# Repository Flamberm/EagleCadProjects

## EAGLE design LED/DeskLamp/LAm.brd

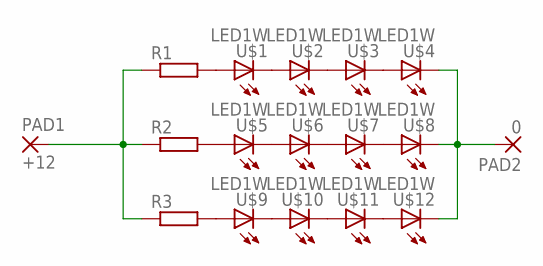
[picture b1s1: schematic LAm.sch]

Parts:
PAD1: +12; SMD2,54-5,08
PAD2: 0; SMD2,54-5,08
R1, R2, R3: R-EU_R0805; R0805
U$1, U$2, U$3, U$4, U$5, U$6, U$7, U$8, U$9, U$10, U$11, U$12: LED1W; LED-1W

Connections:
unnamed: R1.2, U$1.A
unnamed: U$1.K (C), U$2.A
unnamed: U$2.K (C), U$3.A
unnamed: U$3.K (C), U$4.A
unnamed: R2.2, U$5.A
unnamed: U$5.K (C), U$6.A
unnamed: U$6.K (C), U$7.A
unnamed: U$7.K (C), U$8.A
unnamed: R3.2, U$9.A
unnamed: U$9.K (C), U$10.A
unnamed: U$10.K (C), U$11.A
unnamed: U$11.K (C), U$12.A
unnamed: PAD1.1, R1.1, R2.1, R3.1
unnamed: PAD2.1, U$4.K (C), U$8.K (C), U$12.K (C)

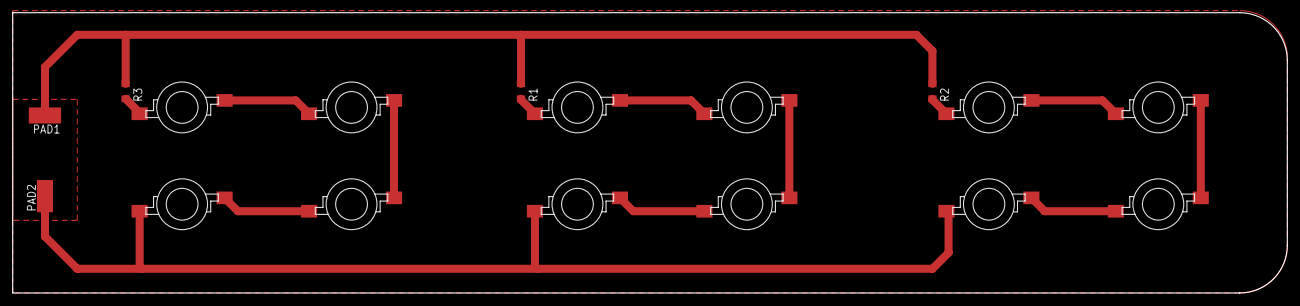
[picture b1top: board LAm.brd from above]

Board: 2 copper layers, 200.6 x 44.1 mm, 17 parts (0 on the bottom side), 14 nets.

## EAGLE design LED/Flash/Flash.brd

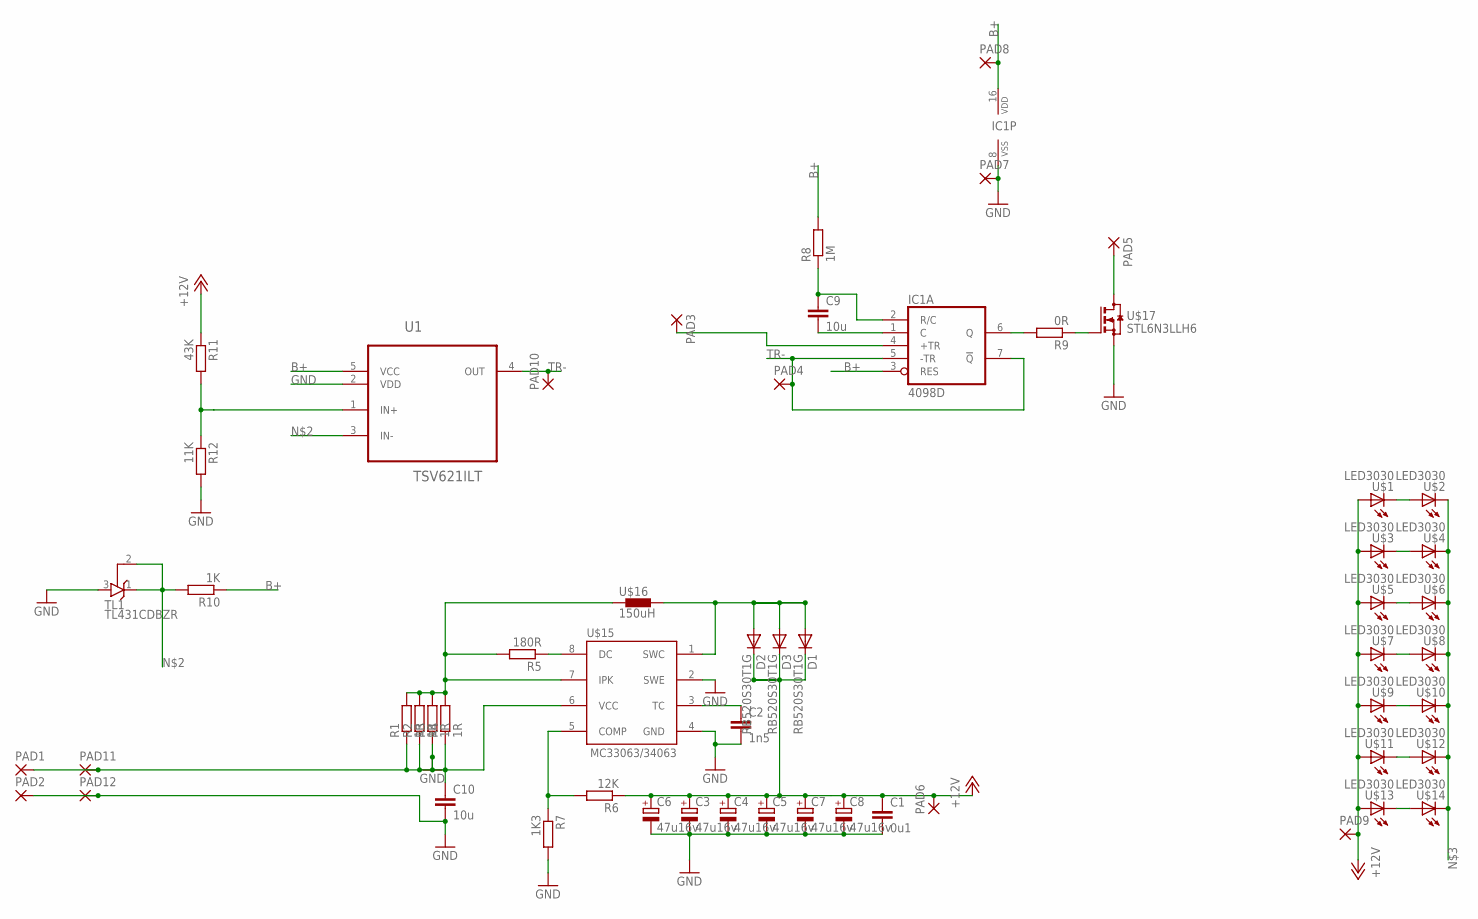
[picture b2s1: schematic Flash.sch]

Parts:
C1: 0u1; C0805
C2: 1n5; C0805
C3, C4, C5, C6, C7, C8: 47u16v; 153CLV-0605
C9: 10u; C0805
C10: 10u; C1206
D1, D2, D3: RB520S30T1G; SOD523
IC1: 4098D; SO16
PAD1, PAD2, PAD3, PAD4, PAD5, PAD6, PAD7, PAD8, PAD9, PAD10, PAD11, PAD12: SMD2; SMD1,27-2,54
R1, R2, R3, R4: 1R; R0805
R5: 180R; R0805
R6: 12K; R0805
R7: 1K3; R0805
R8: 1M; R0805
R9: 0R; R0805
R10: 1K; R0805
R11: 43K; R0805
R12: 11K; R0805
TL1: TL431CDBZR; SOT23
U1: TSV621ILT; SOT95P280X145-5N
U$1, U$2, U$3, U$4, U$5, U$6, U$7, U$8, U$9, U$10, U$11, U$12, U$13, U$14: LED3030
U$15: MC33063/MC34063D; SO08
U$16: 150uH; L6045
U$17: STL6N3LLH6; POWERFLAT-2X2

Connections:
+12V: C1.1, C3.+, C4.+, C5.+, C6.+, C7.+, C8.+, D1.C, D2.C, D3.C, PAD6.1, PAD9.1, R6.1, R11.1, U$1.P$1 (A), U$3.P$1 (A), U$5.P$1 (A), U$7.P$1 (A), U$9.P$1 (A), U$11.P$1 (A), U$13.P$1 (A)
B+: C10.1, IC1.3 (RES), IC1.16 (VDD), PAD1.1, PAD8.1, PAD11.1, R1.1, R2.1, R3.1, R4.1, R8.2, R10.1, U1.5 (VCC), U$15.6 (VCC)
GND: C1.2, C2.2, C3.-, C4.-, C5.-, C6.-, C7.-, C8.-, C10.2, IC1.8 (VSS), PAD2.1, PAD7.1, PAD12.1, R7.2, R12.2, TL1.3 (A), U1.2 (VDD), U$15.2 (SWE), U$15.4 (GND), U$17.S, U$17.S4 (S)
unnamed: U$1.P$2 (C), U$2.P$1 (A)
unnamed: R10.2, TL1.1 (C), TL1.2 (R), U1.3 (IN-)
unnamed: PAD5.1, U$2.P$2 (C), U$4.P$2 (C), U$6.P$2 (C), U$8.P$2 (C), U$10.P$2 (C), U$12.P$2 (C), U$14.P$2 (C), U$17.D, U$17.D1 (D), U$17.D2 (D), U$17.D5 (D), U$17.D6 (D)
unnamed: U$3.P$2 (C), U$4.P$1 (A)
unnamed: R11.2, R12.1, U1.1 (IN+)
unnamed: IC1.4 (+TR), PAD3.1
unnamed: U$5.P$2 (C), U$6.P$1 (A)
unnamed: R1.2, R2.2, R3.2, R4.2, R5.2, U$15.7 (IPK), U$16.P$1 (1)
unnamed: R5.1, U$15.8 (DC)
unnamed: U$7.P$2 (C), U$8.P$1 (A)
unnamed: R6.2, R7.1, U$15.5 (COMP)
unnamed: D1.A, D2.A, D3.A, U$15.1 (SWC), U$16.P$2 (2)
unnamed: U$9.P$2 (C), U$10.P$1 (A)
unnamed: C2.1, U$15.3 (TC)
unnamed: U$11.P$2 (C), U$12.P$1 (A)
unnamed: C9.2, IC1.1 (C)
unnamed: C9.1, IC1.2 (R/C), R8.1
unnamed: U$13.P$2 (C), U$14.P$1 (A)
unnamed: IC1.6 (Q), R9.2
unnamed: R9.1, U$17.G3 (G)
TR-: IC1.5 (-TR), IC1.7 (!Q), PAD4.1, PAD10.1, U1.4 (OUT)

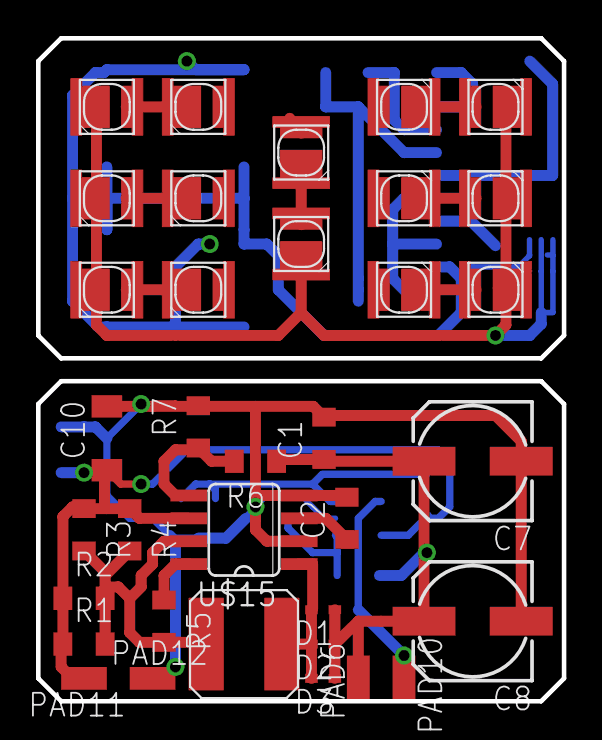
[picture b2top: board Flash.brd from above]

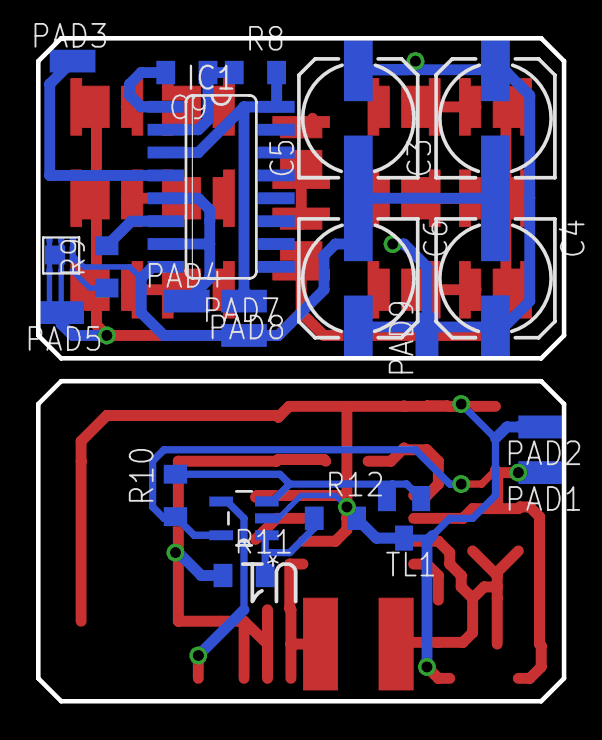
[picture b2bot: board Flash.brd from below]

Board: 2 copper layers, 29.2 x 36.8 mm, 57 parts (22 on the bottom side), 24 nets.

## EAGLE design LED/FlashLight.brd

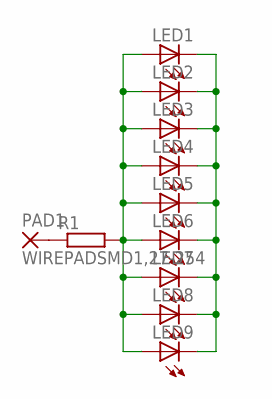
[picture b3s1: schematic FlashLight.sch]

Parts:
LED1, LED2, LED3, LED4, LED5, LED6, LED7, LED8, LED9: LED5MM
PAD1: WIREPADSMD1,27-254; SMD1,27-2,54
R1: R-EU_R1206; R1206

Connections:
unnamed: LED1.A, LED2.A, LED3.A, LED4.A, LED5.A, LED6.A, LED7.A, LED8.A, LED9.A, R1.2
unnamed: LED1.K (C), LED2.K (C), LED3.K (C), LED4.K (C), LED5.K (C), LED6.K (C), LED7.K (C), LED8.K (C), LED9.K (C)
unnamed: PAD1.1, R1.1

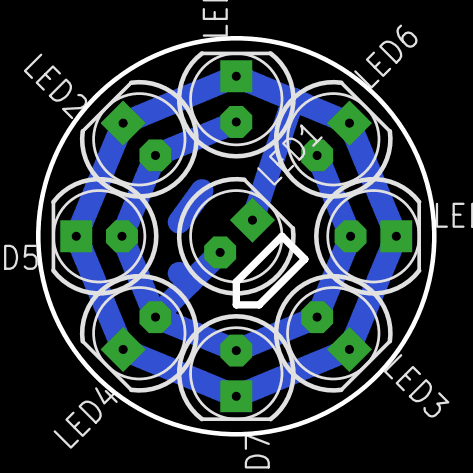
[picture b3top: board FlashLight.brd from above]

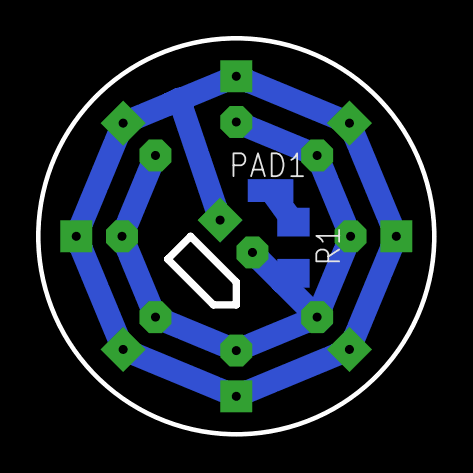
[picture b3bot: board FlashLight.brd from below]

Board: 2 copper layers, 22.0 x 22.0 mm, 11 parts (2 on the bottom side), 3 nets.

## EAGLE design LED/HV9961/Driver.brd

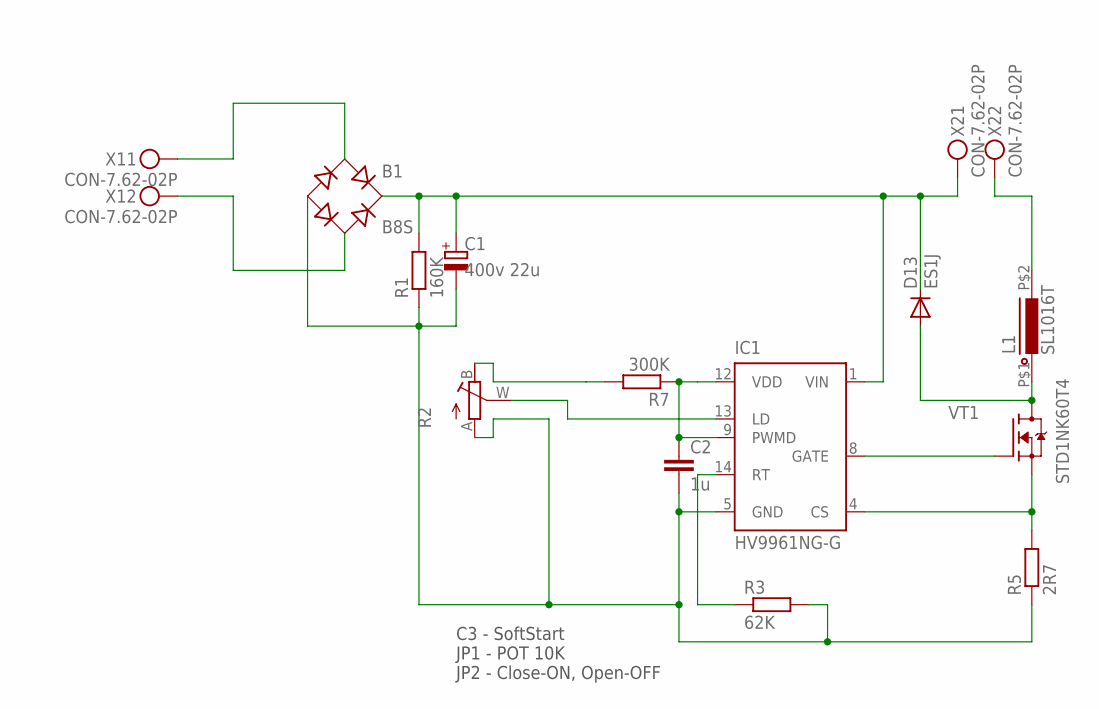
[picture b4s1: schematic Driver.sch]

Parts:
B1: B8S; DFS
C1: 400v 22u; E3,5-8
C2: 1u; C0805
D13: ES1J; DO214AC
IC1: HV9961NG-G; SOIC-16NG
L1: SL1016T; SL1016
R1: 160K; MF-0125
R2: R_POTTURN-X; RJ9W
R3: 62K; R0805
R5: 2R7; MF-025
R7: 300K; R0805
VT1: STD1NK60T4; DPAK
X1, X2: CON-7.62-02P; KF25C-7.62-02P-13

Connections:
unnamed: R2.B (E), R7.2
unnamed: C2.1, IC1.9 (PWMD), IC1.12 (VDD), R7.1
unnamed: B1.AC1, X1.P$1
unnamed: B1.AC2, X1.P$2
unnamed: B1.-, C1.-, C2.2, IC1.5 (GND), R1.1, R2.A, R3.2, R5.1
unnamed: IC1.13 (LD), R2.W (S)
unnamed: B1.+, C1.+, D13.C, IC1.1 (VIN), R1.2, X2.P$1
unnamed: IC1.4 (CS), R5.2, VT1.S
unnamed: IC1.14 (RT), R3.1
unnamed: IC1.8 (GATE), VT1.G
unnamed: L1.P$2 (2), X2.P$2
unnamed: D13.A, L1.P$1 (1), VT1.D

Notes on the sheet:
C3 - SoftStart JP1 - POT 10K JP2 - Close-ON, Open-OFF

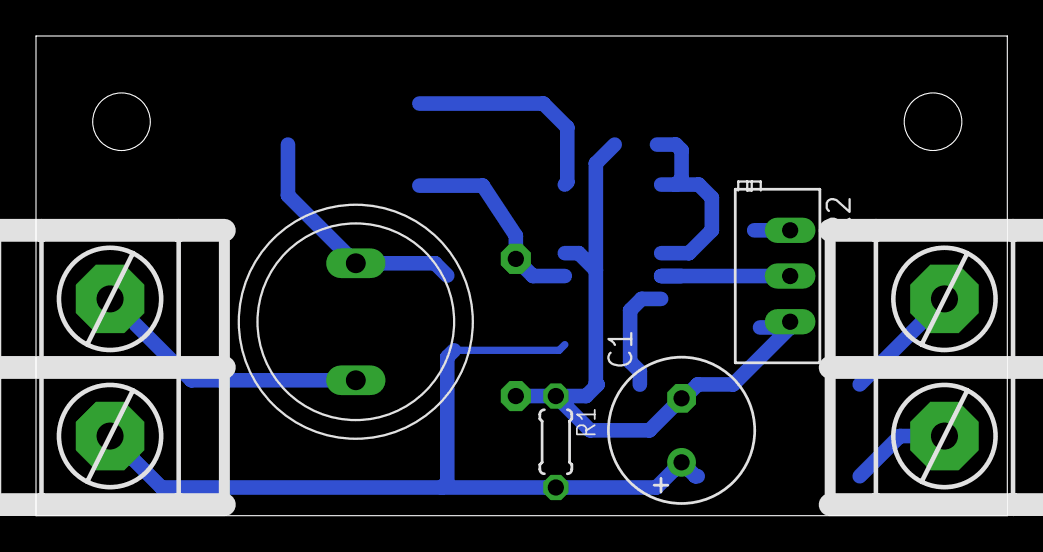
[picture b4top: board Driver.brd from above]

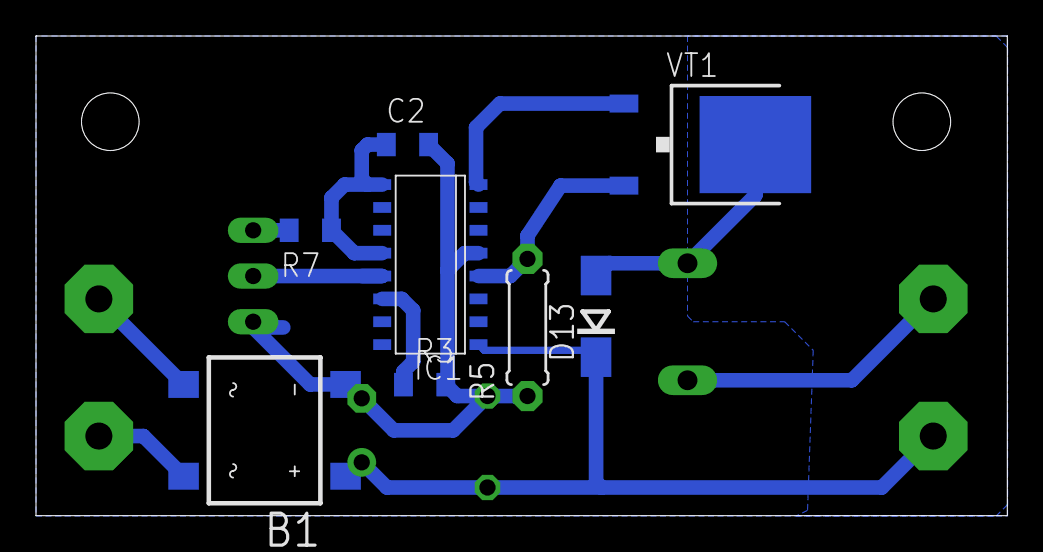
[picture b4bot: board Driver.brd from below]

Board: 2 copper layers, 54.0 x 26.7 mm, 14 parts (8 on the bottom side), 12 nets.

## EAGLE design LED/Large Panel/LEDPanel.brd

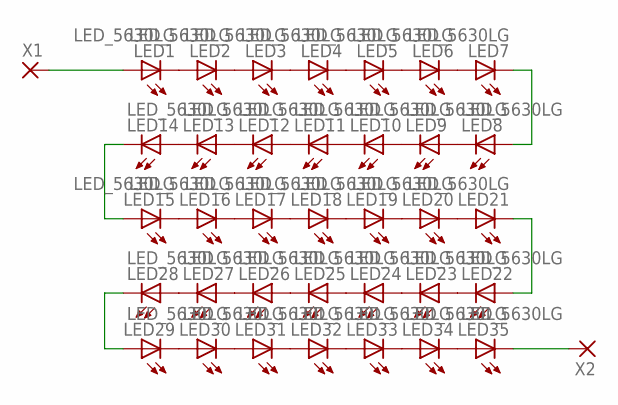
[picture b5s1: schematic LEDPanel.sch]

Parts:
LED1, LED2, LED3, LED4, LED5, LED6, LED7, LED8, LED9, LED10, LED11, LED12, LED13, LED14, LED15, LED16, LED17, LED18, LED19, LED20, LED21, LED22, LED23, LED24, LED25, LED26, LED27, LED28, LED29, LED30, LED31, LED32, LED33, LED34, LED35: LED_5630LG; LED5630_LG
X1, X2: WIREPAD-SMD2; PAD-1.27X2.54

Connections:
1: LED1.A1 (A), LED1.A2 (A), LED1.A-TAB (A), X1.P$1
2: LED1.C1 (C), LED1.C-NC (C), LED2.A1 (A), LED2.A2 (A), LED2.A-TAB (A)
3: LED2.C1 (C), LED2.C-NC (C), LED3.A1 (A), LED3.A2 (A), LED3.A-TAB (A)
4: LED3.C1 (C), LED3.C-NC (C), LED4.A1 (A), LED4.A2 (A), LED4.A-TAB (A)
5: LED4.C1 (C), LED4.C-NC (C), LED5.A1 (A), LED5.A2 (A), LED5.A-TAB (A)
6: LED5.C1 (C), LED5.C-NC (C), LED6.A1 (A), LED6.A2 (A), LED6.A-TAB (A)
7: LED6.C1 (C), LED6.C-NC (C), LED7.A1 (A), LED7.A2 (A), LED7.A-TAB (A)
8: LED7.C1 (C), LED7.C-NC (C), LED8.A1 (A), LED8.A2 (A), LED8.A-TAB (A)
9: LED8.C1 (C), LED8.C-NC (C), LED9.A1 (A), LED9.A2 (A), LED9.A-TAB (A)
10: LED9.C1 (C), LED9.C-NC (C), LED10.A1 (A), LED10.A2 (A), LED10.A-TAB (A)
11: LED10.C1 (C), LED10.C-NC (C), LED11.A1 (A), LED11.A2 (A), LED11.A-TAB (A)
12: LED11.C1 (C), LED11.C-NC (C), LED12.A1 (A), LED12.A2 (A), LED12.A-TAB (A)
13: LED12.C1 (C), LED12.C-NC (C), LED13.A1 (A), LED13.A2 (A), LED13.A-TAB (A)
14: LED13.C1 (C), LED13.C-NC (C), LED14.A1 (A), LED14.A2 (A), LED14.A-TAB (A)
15: LED14.C1 (C), LED14.C-NC (C), LED15.A1 (A), LED15.A2 (A), LED15.A-TAB (A)
16: LED15.C1 (C), LED15.C-NC (C), LED16.A1 (A), LED16.A2 (A), LED16.A-TAB (A)
17: LED16.C1 (C), LED16.C-NC (C), LED17.A1 (A), LED17.A2 (A), LED17.A-TAB (A)
18: LED17.C1 (C), LED17.C-NC (C), LED18.A1 (A), LED18.A2 (A), LED18.A-TAB (A)
19: LED18.C1 (C), LED18.C-NC (C), LED19.A1 (A), LED19.A2 (A), LED19.A-TAB (A)
20: LED19.C1 (C), LED19.C-NC (C), LED20.A1 (A), LED20.A2 (A), LED20.A-TAB (A)
21: LED20.C1 (C), LED20.C-NC (C), LED21.A1 (A), LED21.A2 (A), LED21.A-TAB (A)
22: LED21.C1 (C), LED21.C-NC (C), LED22.A1 (A), LED22.A2 (A), LED22.A-TAB (A)
23: LED22.C1 (C), LED22.C-NC (C), LED23.A1 (A), LED23.A2 (A), LED23.A-TAB (A)
24: LED23.C1 (C), LED23.C-NC (C), LED24.A1 (A), LED24.A2 (A), LED24.A-TAB (A)
25: LED24.C1 (C), LED24.C-NC (C), LED25.A1 (A), LED25.A2 (A), LED25.A-TAB (A)
26: LED25.C1 (C), LED25.C-NC (C), LED26.A1 (A), LED26.A2 (A), LED26.A-TAB (A)
27: LED26.C1 (C), LED26.C-NC (C), LED27.A1 (A), LED27.A2 (A), LED27.A-TAB (A)
28: LED27.C1 (C), LED27.C-NC (C), LED28.A1 (A), LED28.A2 (A), LED28.A-TAB (A)
29: LED28.C1 (C), LED28.C-NC (C), LED29.A1 (A), LED29.A2 (A), LED29.A-TAB (A)
30: LED29.C1 (C), LED29.C-NC (C), LED30.A1 (A), LED30.A2 (A), LED30.A-TAB (A)
31: LED30.C1 (C), LED30.C-NC (C), LED31.A1 (A), LED31.A2 (A), LED31.A-TAB (A)
32: LED31.C1 (C), LED31.C-NC (C), LED32.A1 (A), LED32.A2 (A), LED32.A-TAB (A)
33: LED32.C1 (C), LED32.C-NC (C), LED33.A1 (A), LED33.A2 (A), LED33.A-TAB (A)
34: LED33.C1 (C), LED33.C-NC (C), LED34.A1 (A), LED34.A2 (A), LED34.A-TAB (A)
35: LED34.C1 (C), LED34.C-NC (C), LED35.A1 (A), LED35.A2 (A), LED35.A-TAB (A)
36: LED35.C1 (C), LED35.C-NC (C), X2.P$1

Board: 2 copper layers, 37 parts (0 on the bottom side), 36 nets, no tracks yet.

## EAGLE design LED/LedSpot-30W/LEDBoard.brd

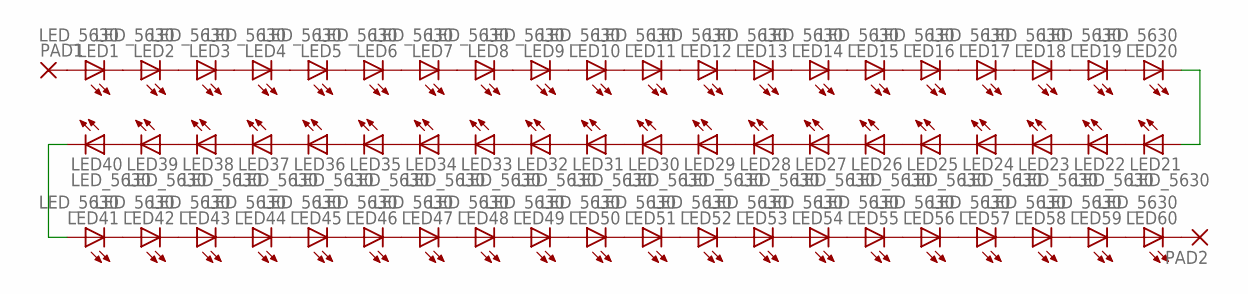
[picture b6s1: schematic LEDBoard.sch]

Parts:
LED1, LED2, LED3, LED4, LED5, LED6, LED7, LED8, LED9, LED10, LED11, LED12, LED13, LED14, LED15, LED16, LED17, LED18, LED19, LED20, LED21, LED22, LED23, LED24, LED25, LED26, LED27, LED28, LED29, LED30, LED31, LED32, LED33, LED34, LED35, LED36, LED37, LED38, LED39, LED40, LED41, LED42, LED43, LED44, LED45, LED46, LED47, LED48, LED49, LED50, LED51, LED52, LED53, LED54, LED55, LED56, LED57, LED58, LED59, LED60: LED_5630; LED5730
PAD1, PAD2: SMD5; SMD2,54-5,08

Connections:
unnamed: LED1.C, LED2.A, LED2.A1 (A)
unnamed: LED3.C, LED4.A, LED4.A1 (A)
unnamed: LED2.C, LED3.A, LED3.A1 (A)
unnamed: LED5.C, LED6.A, LED6.A1 (A)
unnamed: LED7.C, LED8.A, LED8.A1 (A)
unnamed: LED6.C, LED7.A, LED7.A1 (A)
unnamed: LED4.C, LED5.A, LED5.A1 (A)
unnamed: LED9.C, LED10.A, LED10.A1 (A)
unnamed: LED11.C, LED12.A, LED12.A1 (A)
unnamed: LED10.C, LED11.A, LED11.A1 (A)
unnamed: LED13.C, LED14.A, LED14.A1 (A)
unnamed: LED15.C, LED16.A, LED16.A1 (A)
unnamed: LED14.C, LED15.A, LED15.A1 (A)
unnamed: LED12.C, LED13.A, LED13.A1 (A)
unnamed: LED8.C, LED9.A, LED9.A1 (A)
unnamed: LED17.C, LED18.A, LED18.A1 (A)
unnamed: LED19.C, LED20.A, LED20.A1 (A)
unnamed: LED18.C, LED19.A, LED19.A1 (A)
unnamed: LED16.C, LED17.A, LED17.A1 (A)
unnamed: LED21.C, LED22.A, LED22.A1 (A)
unnamed: LED23.C, LED24.A, LED24.A1 (A)
unnamed: LED22.C, LED23.A, LED23.A1 (A)
unnamed: LED25.C, LED26.A, LED26.A1 (A)
unnamed: LED27.C, LED28.A, LED28.A1 (A)
unnamed: LED26.C, LED27.A, LED27.A1 (A)
unnamed: LED24.C, LED25.A, LED25.A1 (A)
unnamed: LED29.C, LED30.A, LED30.A1 (A)
unnamed: LED31.C, LED32.A, LED32.A1 (A)
unnamed: LED30.C, LED31.A, LED31.A1 (A)
unnamed: LED33.C, LED34.A, LED34.A1 (A)
unnamed: LED35.C, LED36.A, LED36.A1 (A)
unnamed: LED34.C, LED35.A, LED35.A1 (A)
unnamed: LED32.C, LED33.A, LED33.A1 (A)
unnamed: LED28.C, LED29.A, LED29.A1 (A)
unnamed: LED37.C, LED38.A, LED38.A1 (A)
unnamed: LED39.C, LED40.A, LED40.A1 (A)
unnamed: LED38.C, LED39.A, LED39.A1 (A)
unnamed: LED36.C, LED37.A, LED37.A1 (A)
unnamed: LED41.C, LED42.A, LED42.A1 (A)
unnamed: LED43.C, LED44.A, LED44.A1 (A)
unnamed: LED42.C, LED43.A, LED43.A1 (A)
unnamed: LED45.C, LED46.A, LED46.A1 (A)
unnamed: LED47.C, LED48.A, LED48.A1 (A)
unnamed: LED46.C, LED47.A, LED47.A1 (A)
unnamed: LED44.C, LED45.A, LED45.A1 (A)
unnamed: LED49.C, LED50.A, LED50.A1 (A)
unnamed: LED51.C, LED52.A, LED52.A1 (A)
unnamed: LED50.C, LED51.A, LED51.A1 (A)
unnamed: LED53.C, LED54.A, LED54.A1 (A)
unnamed: LED55.C, LED56.A, LED56.A1 (A)
unnamed: LED54.C, LED55.A, LED55.A1 (A)
unnamed: LED52.C, LED53.A, LED53.A1 (A)
unnamed: LED48.C, LED49.A, LED49.A1 (A)
unnamed: LED57.C, LED58.A, LED58.A1 (A)
unnamed: LED59.C, LED60.A, LED60.A1 (A)
unnamed: LED58.C, LED59.A, LED59.A1 (A)
unnamed: LED56.C, LED57.A, LED57.A1 (A)
unnamed: LED20.C, LED21.A, LED21.A1 (A)
unnamed: LED40.C, LED41.A, LED41.A1 (A)
unnamed: LED1.A, LED1.A1 (A), PAD1.1
unnamed: LED60.C, PAD2.1

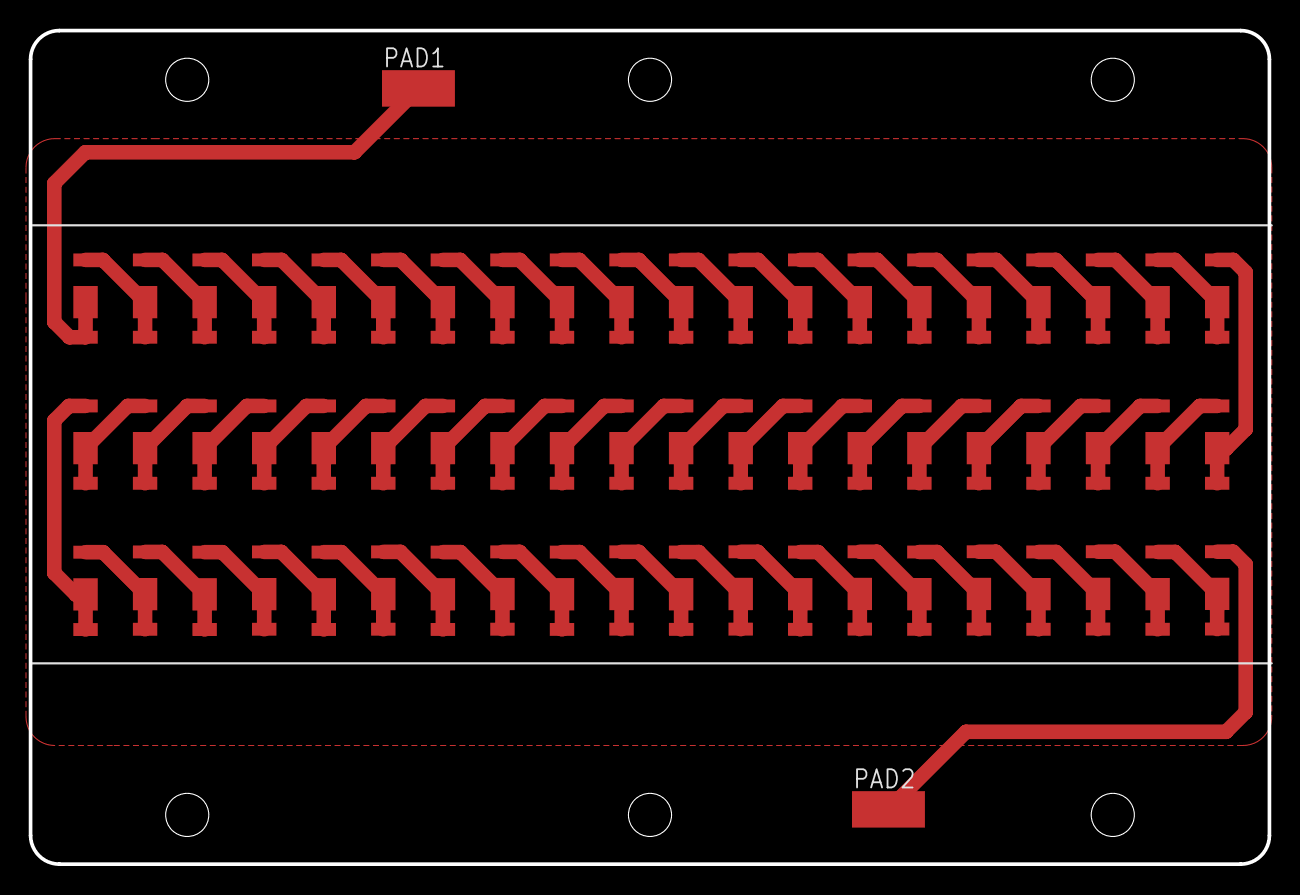
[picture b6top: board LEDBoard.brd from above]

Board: 2 copper layers, 86.2 x 58.0 mm, 62 parts (0 on the bottom side), 61 nets.
